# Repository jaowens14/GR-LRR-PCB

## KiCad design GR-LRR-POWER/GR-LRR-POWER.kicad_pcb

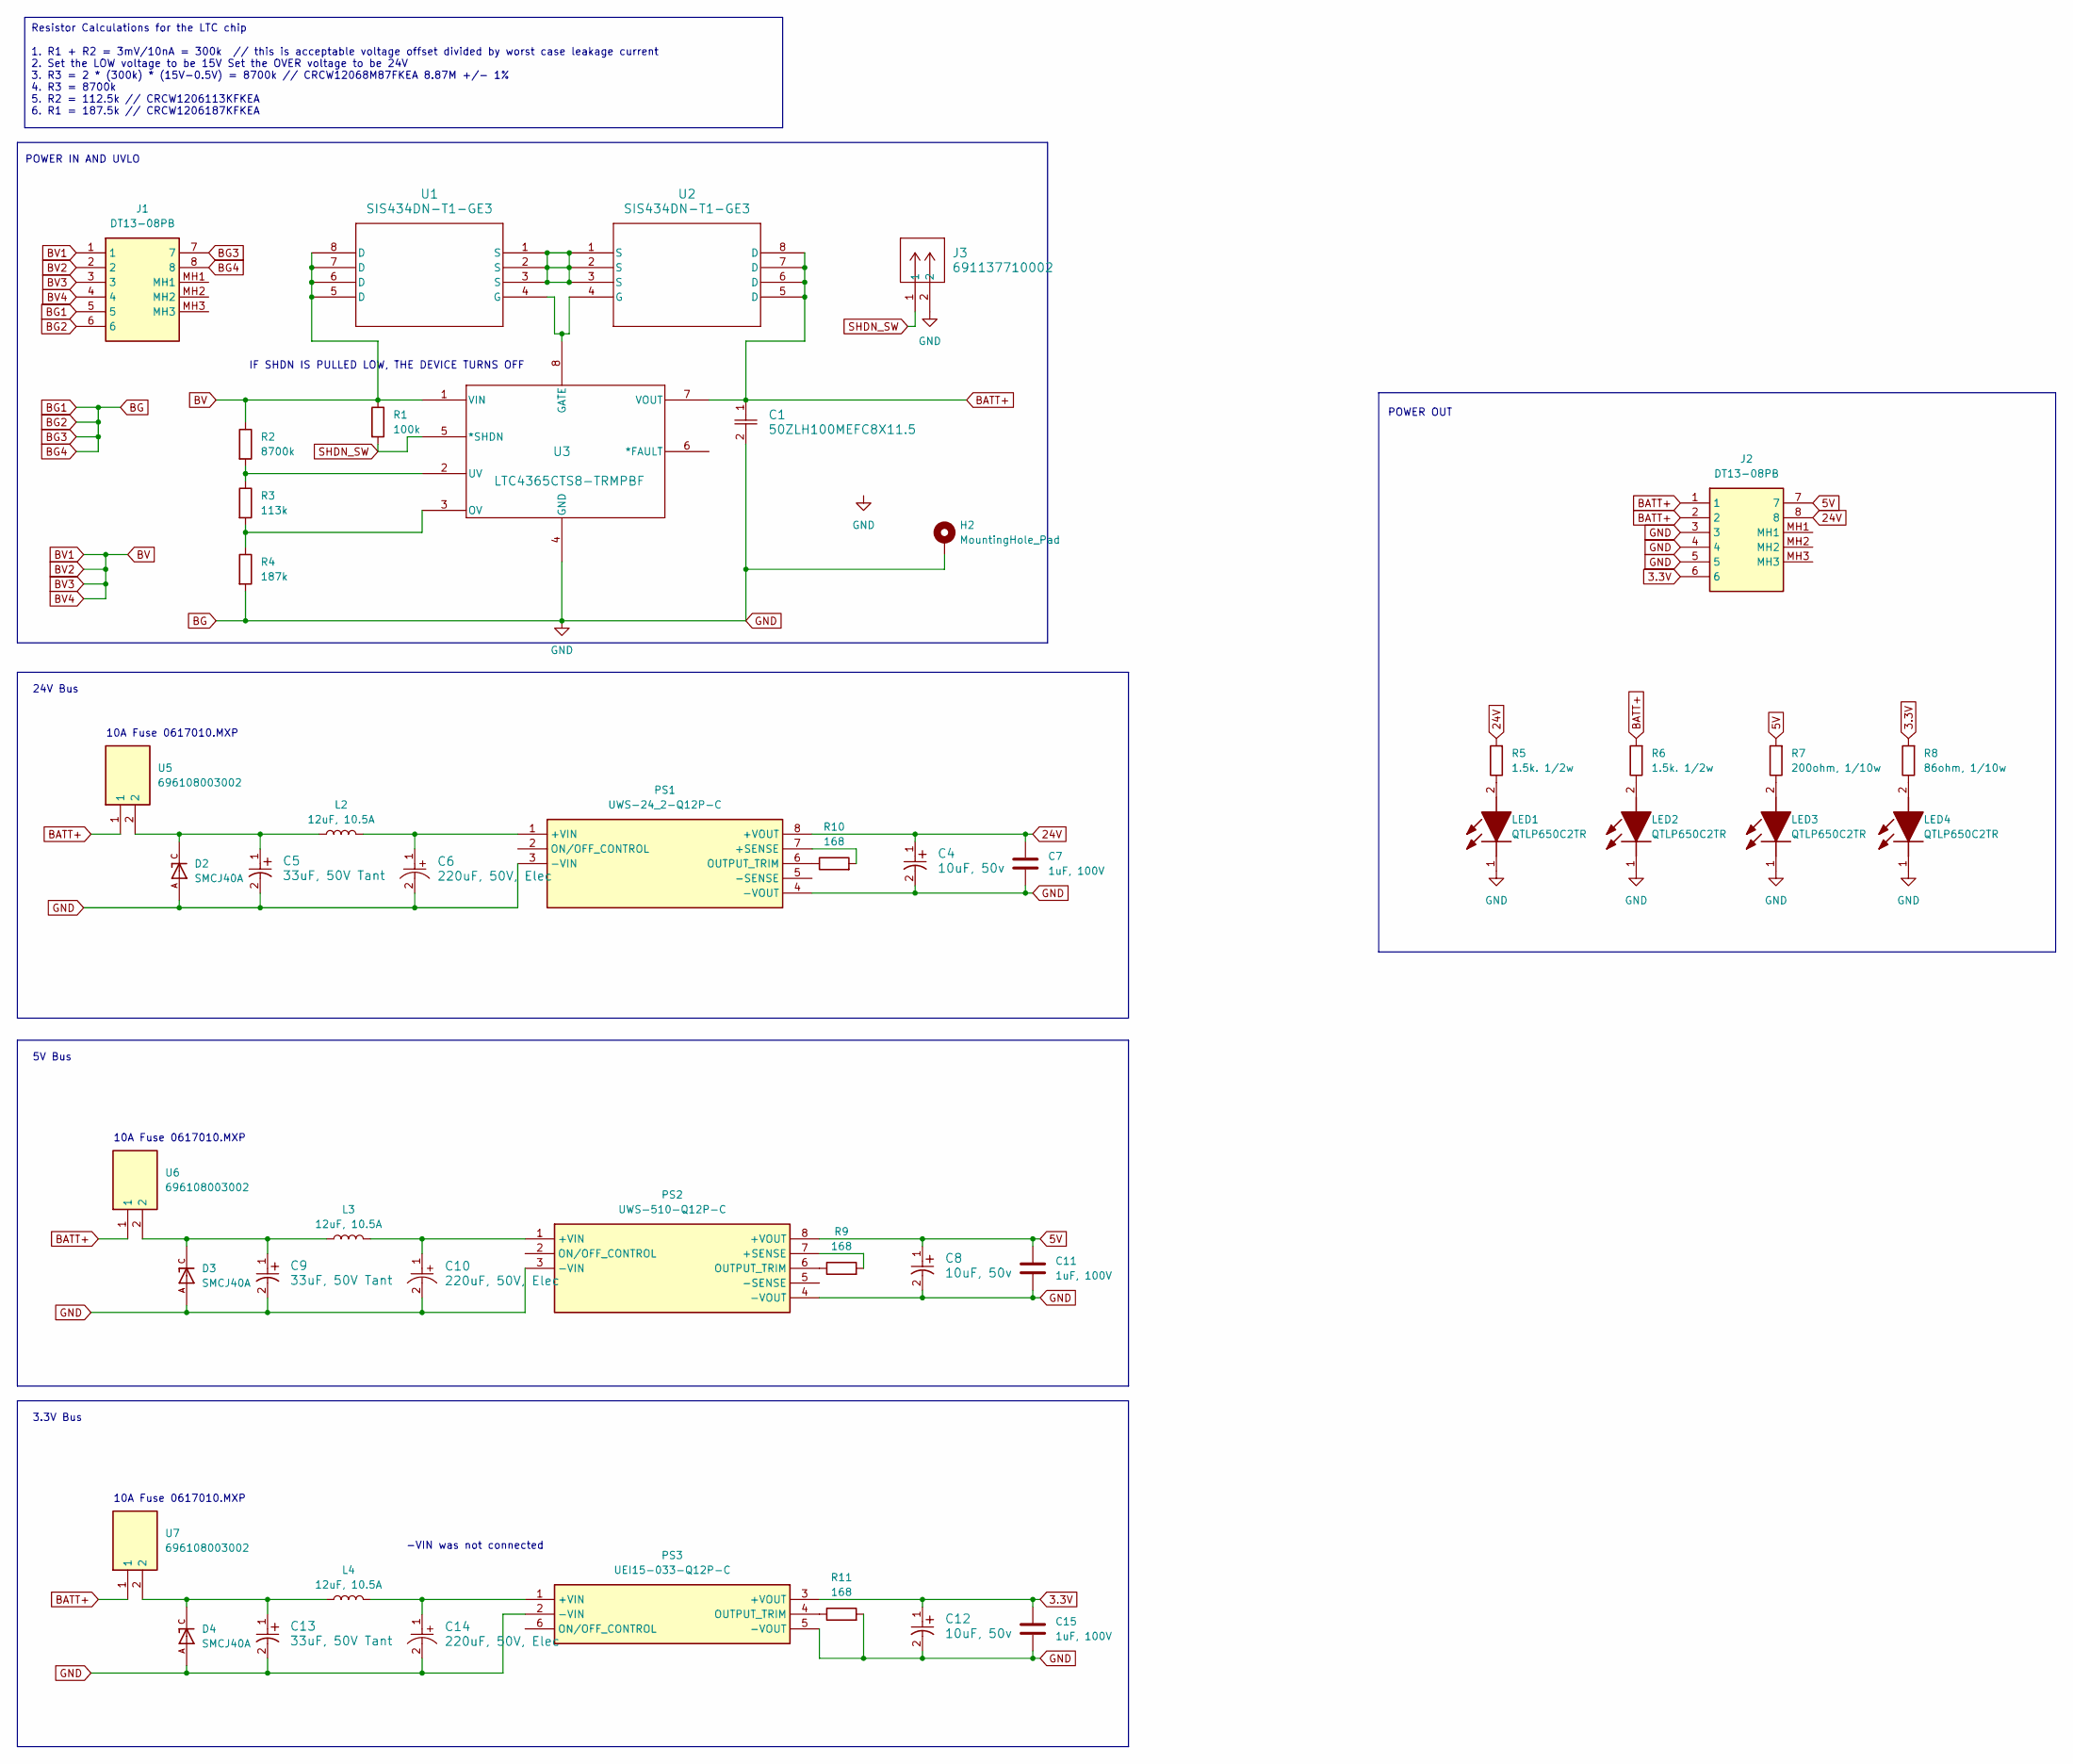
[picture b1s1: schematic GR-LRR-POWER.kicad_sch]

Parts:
C1: 50ZLH100MEFC8X11.5; 50ZLH100MEFC8X11_5; Part Number 50ZLH100MEFC8X11.5
C4, C8, C12: 10uF, 50v; PCAP_6.3x5.4-ELECT_NCA-L; Part Number UWZ1H100MCL1GB
C5, C9, C13: 33uF, 50V Tant; CAPMP7.6X4.3_4.3N_KEM-L; Part Number T521X336M050ATE050
C6, C10, C14: 220uF, 50V, Elec; U2-R_NCH-L; Part Number UWT1H221MNL1GS
C7, C11, C15: 1uF, 100V; C_1206_3216Metric_Pad1.33x1.80mm_HandSolder; Part Number CL31B105KCHNNNE
D2, D3, D4: SMCJ40A; DIOM7959X262N; PARTREV 11/20/15
H2: MountingHole_Pad; MountingHole_3mm_Pad_Via
J1, J2: DT13-08PB; DT1308PB; Mouser Part Number 571-DT13-08PB
J3: 691137710002; Part Number 691137710002
L2, L3, L4: 12uF, 10.5A; L_Coilcraft_XAL8080-XXX; Part Number XAL8080-123
LED1, LED2, LED3, LED4: QTLP650C2TR; LEDC3216X130N; Mouser Part Number 638-QTLP650C2
PS1: UWS-24_2-Q12P-C; UWS242Q12PC; Mouser Part Number 580-UWS-24/2-Q12P-C
PS2: UWS-510-Q12P-C; Mouser Part Number 580-UWS-15/3-Q12P-C
PS3: UEI15-033-Q12P-C; UEI15033Q12PC; Mouser Part Number 580-UEI15-033-Q12P-C
R1: 100k; R_1206_3216Metric_Pad1.30x1.75mm_HandSolder; Part Number CRCW12068M87FKEA
R2: 8700k; R_1206_3216Metric_Pad1.30x1.75mm_HandSolder; Part Number CRCW12068M87FKEA
R3: 113k; R_1206_3216Metric_Pad1.30x1.75mm_HandSolder; Part Number CRCW1206113KFKEA
R4: 187k; R_1206_3216Metric_Pad1.30x1.75mm_HandSolder; Part Number CRCW1206187KFKEA
R5, R6: 1.5k. 1/2w; R_1206_3216Metric_Pad1.30x1.75mm_HandSolder; Part Number RNCP1206FTD1K50
R7: 200ohm, 1/10w; R_1206_3216Metric_Pad1.30x1.75mm_HandSolder; Part Number RMCF1206JT200R
R8: 86ohm, 1/10w; R_1206_3216Metric_Pad1.30x1.75mm_HandSolder; Part Number RC1206FR-0786R6L
R9, R10, R11: 168; R_1206_3216Metric_Pad1.30x1.75mm_HandSolder
U1, U2: SIS434DN-T1-GE3; MOSFET_4DN-T1-E3_VIS; Part Number SIS434DN-T1-GE3
U3: LTC4365CTS8-TRMPBF; TSOT-23_TS8_LIT; Part Number LTC4365CTS8-TRMPBF
U5, U6, U7: 696108003002; WR-FSH_THT_2; Mouser Part Number 710-696108003002

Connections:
3.3V: C12.1, C15.1, J2.6, PS3.3 (+VOUT), R8.2
5V: C8.1, C11.1, J2.7, PS2.8 (+VOUT), R7.2
24V: C4.1, C7.1, J2.8, PS1.8 (+VOUT), R5.2
BATT+: C1.1, J2.1, J2.2, R6.2, U2.5 (D), U2.6 (D), U2.7 (D), U2.8 (D), U3.7 (VOUT), U5.1, U6.1, U7.1
BG: C1.2, C4.2, C5.2, C6.2, C7.2, C8.2, C9.2, C10.2, C11.2, C12.2, C13.2, C14.2, C15.2, D2.A, D3.A, D4.A, H2.1, J1.5, J1.6, J1.7, J1.8, J2.3, J2.4, J2.5, J3.2, LED1.1 (K), LED2.1 (K), LED3.1 (K), LED4.1 (K), PS1.3 (-VIN), PS1.4 (-VOUT), PS2.3 (-VIN), PS2.4 (-VOUT), PS3.2 (-VIN), PS3.5 (-VOUT), R4.2, R11.2, U3.4 (GND)
BV: J1.1, J1.2, J1.3, J1.4, R1.1, R2.1, U1.5 (D), U1.6 (D), U1.7 (D), U1.8 (D), U3.1 (VIN)
unnamed: C5.1, D2.C, L2.1, U5.2
unnamed: C9.1, D3.C, L3.1, U6.2
unnamed: C13.1, D4.C, L4.1, U7.2
unnamed: LED1.2 (A), R5.1
unnamed: LED2.2 (A), R6.1
unnamed: LED3.2 (A), R7.1
unnamed: LED4.2 (A), R8.1
unnamed: PS1.7 (+SENSE), R10.2
unnamed: C6.1, L2.2, PS1.1 (+VIN)
unnamed: PS1.6 (OUTPUT_TRIM), R10.1
unnamed: PS2.7 (+SENSE), R9.2
unnamed: C10.1, L3.2, PS2.1 (+VIN)
unnamed: PS2.6 (OUTPUT_TRIM), R9.1
unnamed: C14.1, L4.2, PS3.1 (+VIN)
unnamed: PS3.4 (OUTPUT_TRIM), R11.1
unnamed: U1.4 (G), U2.4 (G), U3.8 (GATE)
unnamed: U1.1 (S), U1.2 (S), U1.3 (S), U2.1 (S), U2.2 (S), U2.3 (S)
unnamed: R3.2, R4.1, U3.3 (OV)
unnamed: R2.2, R3.1, U3.2 (UV)
SHDN_SW: J3.1, R1.2, U3.5 (*SHDN)

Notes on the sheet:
Resistor Calculations for the LTC chip 1. R1 + R2 = 3mV/10nA = 300k // this is acceptable voltage offset divided by worst case leakage current 2. Set the LOW voltage to be 15V Set the OVER voltage to be 24V 3. R3 = 2 * (300k) * (15V-0.5V) = 8700k // CRCW12068M87FKEA 8.87M +/- 1% 4. R3 = 8700k 5. R2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
10A Fuse 0617010.MXP
3.3V Bus
POWER IN AND UVLO
POWER OUT
24V Bus
5V Bus
-VIN was not connected
IF SHDN IS PULLED LOW, THE DEVICE TURNS OFF

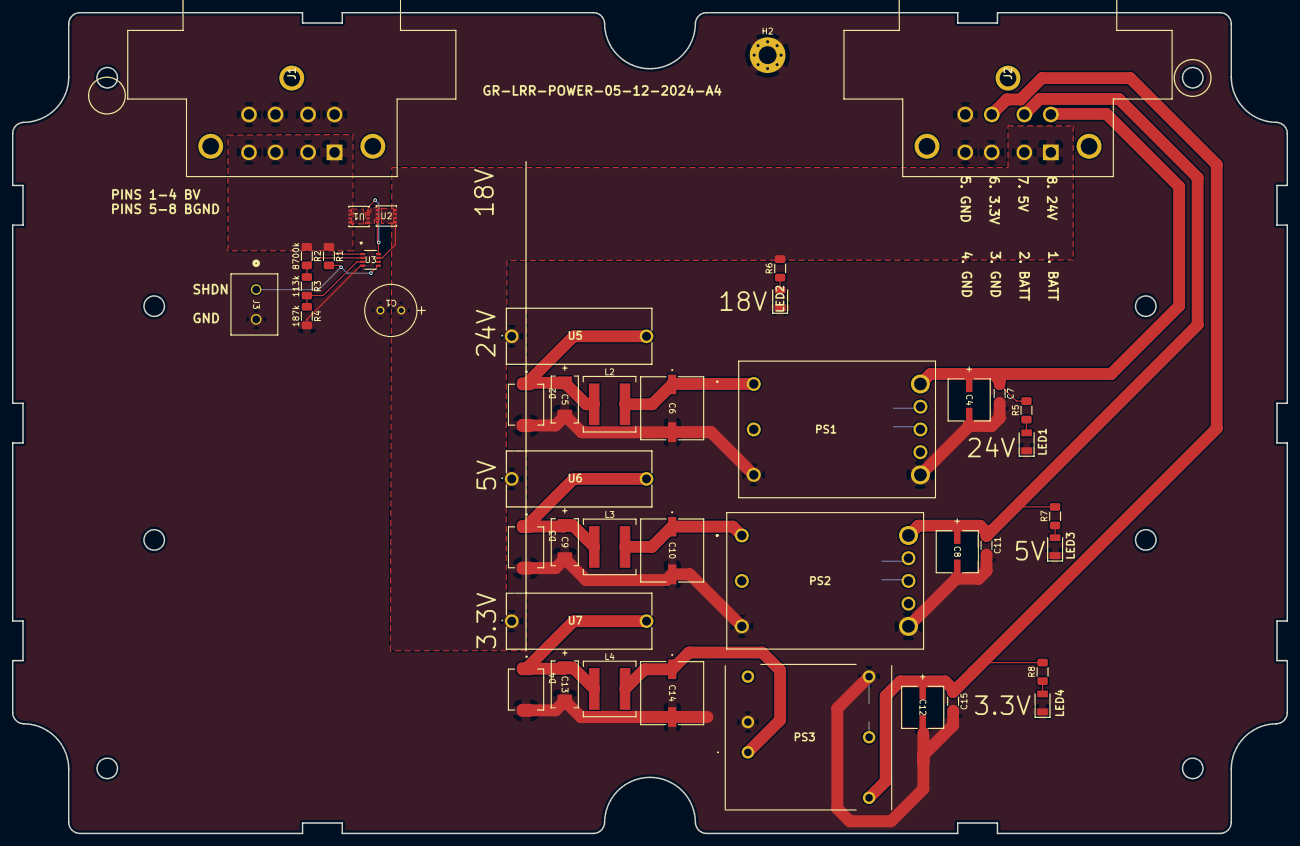
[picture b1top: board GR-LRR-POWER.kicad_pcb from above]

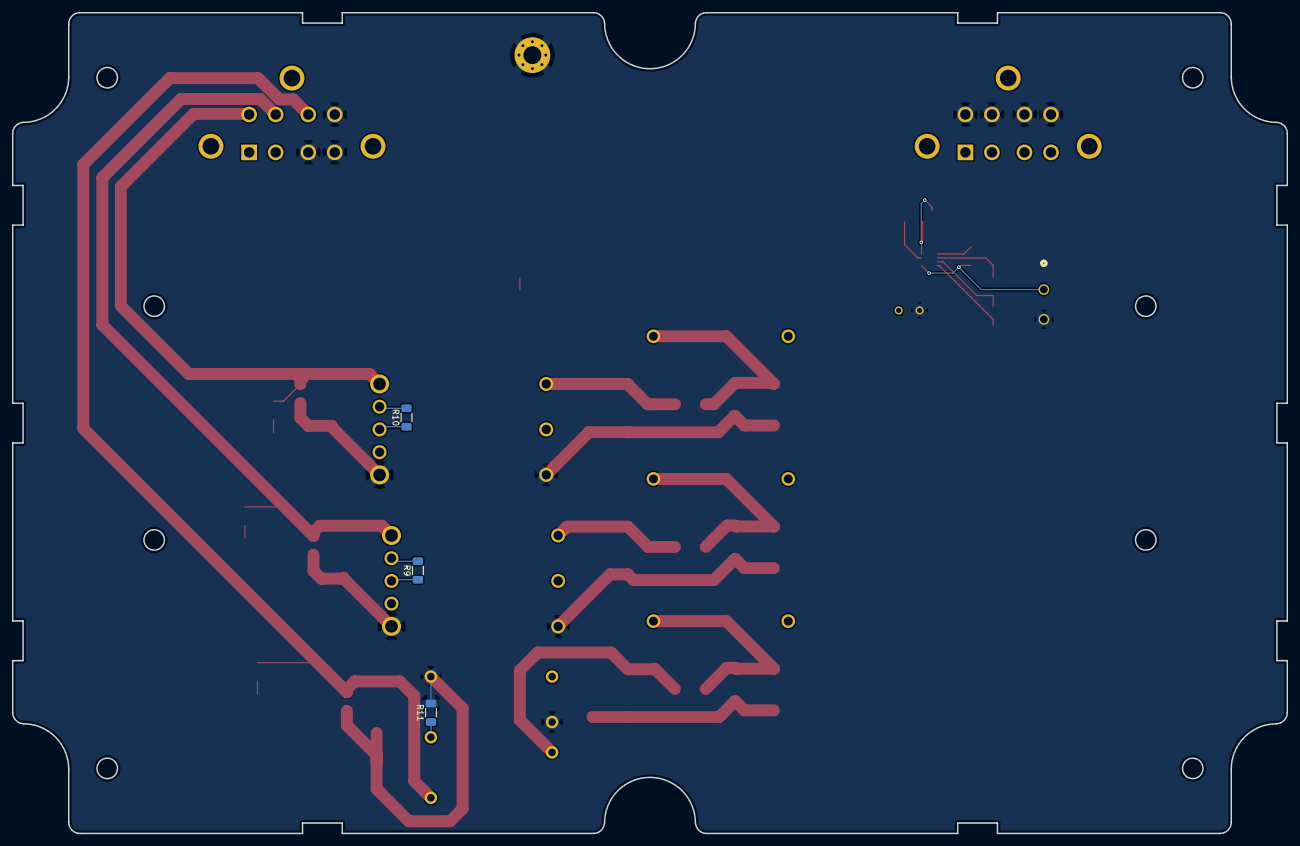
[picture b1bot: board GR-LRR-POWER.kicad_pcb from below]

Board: 2 copper layers, 213.7 x 137.6 mm, 47 parts (3 on the bottom side), 26 nets.

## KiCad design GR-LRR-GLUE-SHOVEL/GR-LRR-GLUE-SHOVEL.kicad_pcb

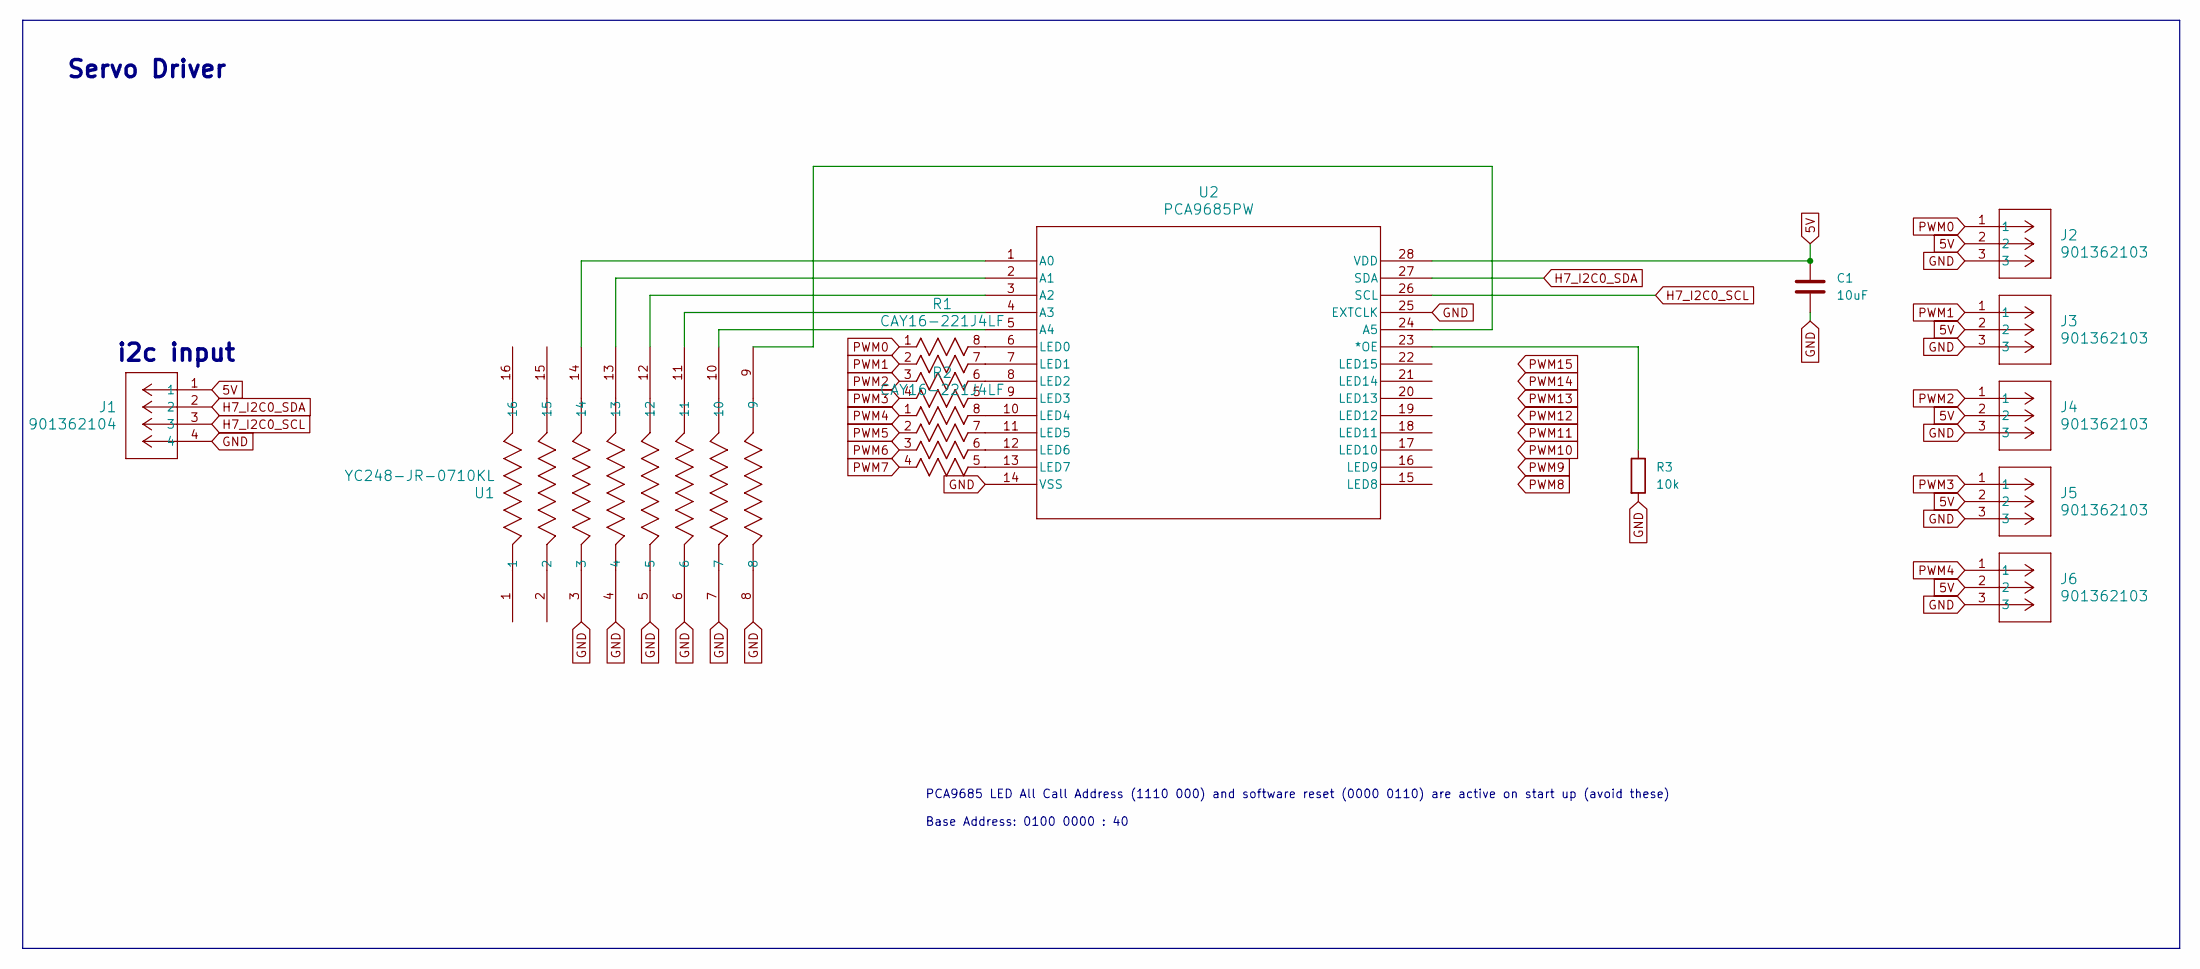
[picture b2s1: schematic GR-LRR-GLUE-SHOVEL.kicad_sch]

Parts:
C1: 10uF; C_1206_3216Metric_Pad1.33x1.80mm_HandSolder
J1: 901362104
J2, J3, J4, J5, J6: 901362103
R1, R2: CAY16-221J4LF; CAY16_221J4LF
R3: 10k; R_1206_3216Metric_Pad1.30x1.75mm_HandSolder
U1: YC248-JR-0710KL; RES_YC248_4X1P6_YAG
U2: PCA9685PW; SOT361-1_NXP

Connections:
5V: C1.1, J1.1, J2.2, J3.2, J4.2, J5.2, J6.2, U2.28 (VDD)
GND: C1.2, J1.4, J2.3, J3.3, J4.3, J5.3, J6.3, R3.2, U1.3, U1.4, U1.5, U1.6, U1.7, U1.8, U2.14 (VSS), U2.25 (EXTCLK)
H7_I2C0_SCL: J1.3, U2.26 (SCL)
H7_I2C0_SDA: J1.2, U2.27 (SDA)
unnamed: R3.1, U2.23 (*OE)
unnamed: U1.14, U2.1 (A0)
unnamed: U1.13, U2.2 (A1)
unnamed: U1.12, U2.3 (A2)
unnamed: U1.11, U2.4 (A3)
unnamed: U1.10, U2.5 (A4)
unnamed: U1.9, U2.24 (A5)
unnamed: R1.8, U2.6 (LED0)
unnamed: R1.7, U2.7 (LED1)
unnamed: R1.6, U2.8 (LED2)
unnamed: R1.5, U2.9 (LED3)
unnamed: R2.8, U2.10 (LED4)
unnamed: R2.7, U2.11 (LED5)
unnamed: R2.6, U2.12 (LED6)
unnamed: R2.5, U2.13 (LED7)
PWM0: J2.1, R1.1
PWM1: J3.1, R1.2
PWM2: J4.1, R1.3
PWM3: J5.1, R1.4
PWM4: J6.1, R2.1
PWM5: R2.2
PWM6: R2.3
PWM7: R2.4

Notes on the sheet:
PCA9685 LED All Call Address (1110 000) and software reset (0000 0110) are active on start up (avoid these) Base Address: 0100 0000 : 40
Servo Driver
i2c input

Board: 2 copper layers, 12 parts (0 on the bottom side), 24 nets, no tracks yet.

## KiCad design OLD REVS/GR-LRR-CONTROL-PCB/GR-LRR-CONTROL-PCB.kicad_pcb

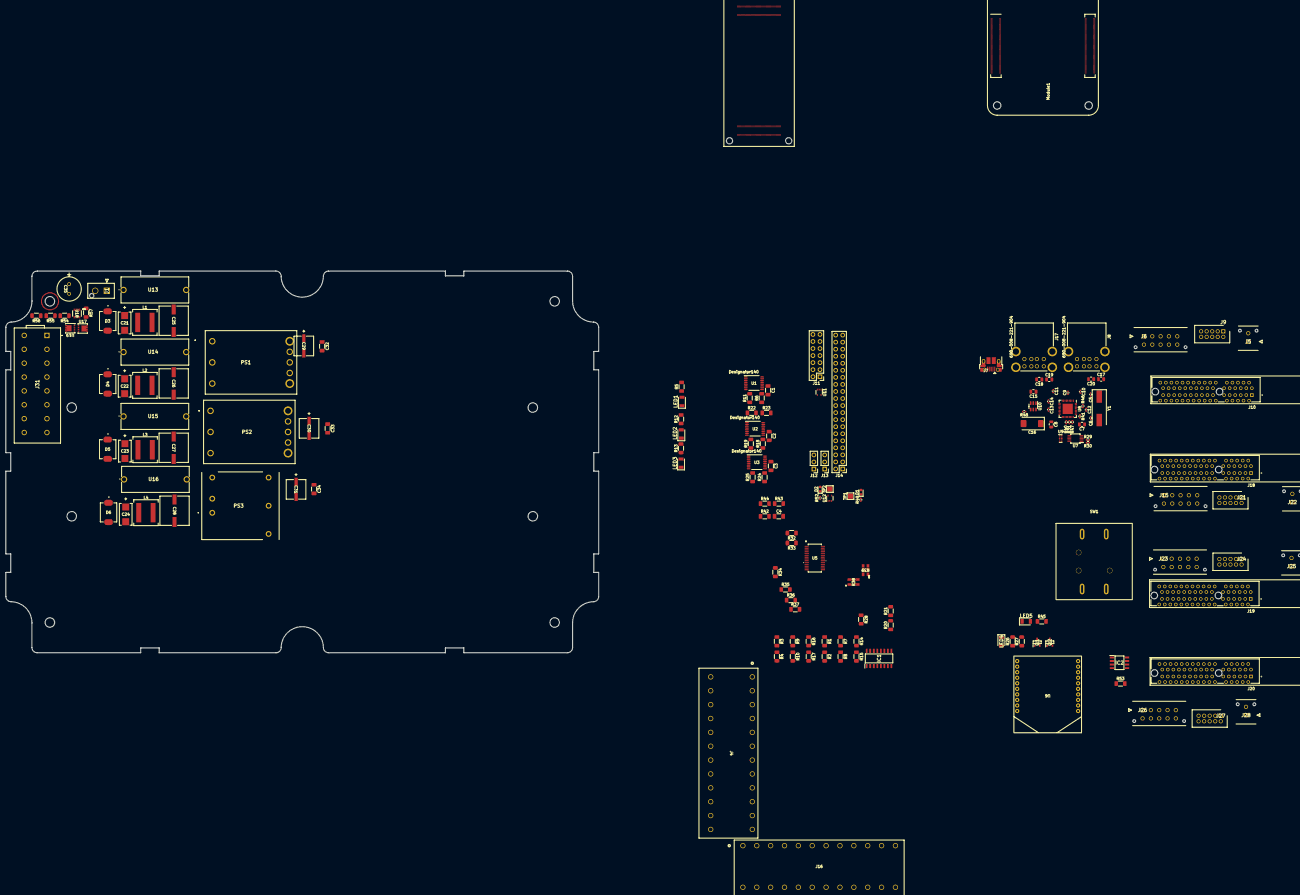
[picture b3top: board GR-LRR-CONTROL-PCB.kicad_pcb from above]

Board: 2 copper layers, 213.7 x 137.6 mm, 163 parts (0 on the bottom side), 228 nets, no tracks yet.

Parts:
C1, C2, C3: 0.1uF; C_1206_3216Metric_Pad1.33x1.80mm_HandSolder
C4: 10uF; C_1206_3216Metric_Pad1.33x1.80mm_HandSolder
C5, C6: 27pF; C_0402_1005Metric
C7, C8, C15, C17, C18, C19, C20: 10u; C_0805_2012Metric
C9, C10, C11, C12, C13, C14: 100n; C_0402_1005Metric
C16: 100uF; CP_EIA-7343-31_Kemet-D
C21, C22, C23, C24: 33uF, 50V Tant; CAPMP7.6X4.3_4.3N_KEM
C25, C26, C27, C28: 220uF, 50V, Elec; U2-R_NCH
C29, C30, C31: 10uF, 50v; PCAP_6.3x5.4-ELECT_NCA
C32, C33, C34: 1uF, 100V; C_1206_3216Metric_Pad1.33x1.80mm_HandSolder
C35: 50ZLH100MEFC8X11.5; CAP_YX_8X11P5_RUB
D1: LED Green; LED_0603_1608Metric
D2: LED Red; LED_0603_1608Metric
D3, D4, D5, D6: SMCJ40A; DIOM7959X262N
IC1: MC1413DR2G; SOIC127P600X175-16N
IC2: TJA1049T,118
J1: Switch; 212520-1002
J4, J16: 736-112; CONN24_736-112_WAG
J5, J22, J25, J28: 43045-0212; 43045-02YY_121314
J6, J15, J23, J26: 43045-1012; 43045-10YY_121314
J7: USB_OTG; USB_Micro-B_EDAC_UCON00686
J8, J17: 690-008-221-904; MOLEX_USB_67298-4090
J9, J21, J24, J27: 87831-1019
J10, J18, J19, J20: 10018783-10101TLF; AMPHENOL_10018783-10101TLF
J11: Conn_02x07_Odd_Even; PinHeader_2x07_P2.54mm_Vertical
J12, J13: Conn_01x03; PinHeader_1x03_P2.54mm_Vertical
J14: THD-20-R; PinHeader_2x20_P2.54mm_Vertical
J31: 2604-3108; 26043108
L1, L2, L3, L4: 12uF, 10.5A; L_Coilcraft_XAL8080-XXX
LED1, LED2, LED3, LED4, LED5: QTLP650C2TR; LEDC3216X130N
Module1: ComputeModule4; Raspberry-Pi-4-Compute-Module
PS1: UWS-24_2-Q12P-C; UWS242Q12PC
PS2: UWS-510-Q12P-C
PS3: UEI15-033-Q12P-C; UEI15033Q12PC
Q1, Q2: BSS806NH6327XTSA1; SOT95P240X110-3N
R1, R3, R7, R9, R14, R16: 1k 1/8W; R_1206_3216Metric_Pad1.30x1.75mm_HandSolder
R2, R4, R8, R10, R15, R17: 2k 1/8w; R_1206_3216Metric_Pad1.30x1.75mm_HandSolder
R5: 1.5k. 1/2w; R_1206_3216Metric_Pad1.30x1.75mm_HandSolder
R6, R11, R18, R19, R24, R25, R32, R33, R34, R35, R36, R37, R42, R43, R44: 10k; R_1206_3216Metric_Pad1.30x1.75mm_HandSolder
R12: 200ohm, 1/10w; R_1206_3216Metric_Pad1.30x1.75mm_HandSolder
R13, R26, R45: 86ohm, 1/10w; R_1206_3216Metric_Pad1.30x1.75mm_HandSolder
R20: 4k; R_1206_3216Metric_Pad1.30x1.75mm_HandSolder
R21: 1k 1/8w; R_1206_3216Metric_Pad1.30x1.75mm_HandSolder
R22: 100k 1/8W; R_1206_3216Metric_Pad1.30x1.75mm_HandSolder
R23: 10k 1/8w; R_1206_3216Metric_Pad1.30x1.75mm_HandSolder
R27, R28: 10k 1/8W; R_1206_3216Metric_Pad1.30x1.75mm_HandSolder
R29, R30: 2.2K 1%; R_0402_1005Metric
R31, R40, R41, R47: 36K 1%; R_0402_1005Metric
R38, R39: CAY16-221J4LF; BO_CAY16
R46: 12K 1%; R_0402_1005Metric
R48: 15K 1%; R_0402_1005Metric
R49, R52: 1k; R_0402_1005Metric
R53: 120; R_1206_3216Metric_Pad1.30x1.75mm_HandSolder
R54: 8700k; R_1206_3216Metric_Pad1.30x1.75mm_HandSolder
R55: 113k; R_1206_3216Metric_Pad1.30x1.75mm_HandSolder
R56: 187k; R_1206_3216Metric_Pad1.30x1.75mm_HandSolder
R57: 100k; R_1206_3216Metric_Pad1.30x1.75mm_HandSolder
SW1: XA1E-BV302-R
TP1, TP2: TestPoint; TestPoint_Pad_2.0x2.0mm
U1, U2, U3: INA260AIPWR; PW0016A_N
U4: ABX00042; MODULE_ABX00042
U5: PCA9685PW; SOT361-1_NXP
U6: XB3-24AST-J
U7: FSUSB42MUX; MSOP-10_3x3mm_P0.5mm
U8: USB2514B-I/M2; QFN-36-1EP_6x6mm_P0.5mm_EP3.7x3.7mm
U9: TPD4EUSB30; USON-10_2.5x1.0mm_P0.5mm
U10: AP22653W6; SOT-23-6
U11, U12: 74LVC1G07SE-7; SOT-353_SC-70-5
U13, U14, U15, U16: 696108003002; WR-FSH_THT_2
U17, U19: SIS434DN-T1-GE3; MOSFET_4DN-T1-E3_VIS
U18: LTC4365CTS8-TRMPBF; TSOT-23_TS8_LIT
Y1: 24MHz; Crystal_SMD_HC49-SD

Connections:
3.3V: C31.1, C34.1, PS3.3 (+VOUT)
5V: C30.1, C33.1, PS2.8 (+VOUT)
18V: C25.1, L1.2
24V: C29.1, C32.1, PS1.8 (+VOUT)
73_ANALOG_A0: R22.2, R23.1, U4.J2_73 (ADC_A0)
75_ANALOG_A1: R20.2, R21.1, U4.J2_75 (ADC_A1)
+3.3V: IC2.5 (SPLIT), Q2.3 (D), R6.1, R11.1, R18.1, R19.1, R24.1, R25.1, R28.1, U3.14 (IN-), U3.15 (IN-), U3.16 (IN-), U6.1 (VCC)
+3.3V_IN: C1.2, C2.2, C3.2, R13.2, U1.10 (VS), U2.10 (VS), U3.1 (IN+), U3.2 (IN+), U3.3 (IN+), U3.5 (A0), U3.10 (VS), U3.12 (VBUS)
+5V: C4.1, IC2.3 (VCC), J4.1, J4.4, J4.7, J4.10, J4.13, J4.16, J4.19, J4.22, J16.15, J16.20, R42.1, R44.1, U2.14 (IN-), U2.15 (IN-), U2.16 (IN-), U4.J1_21 (VIN), U4.J1_41 (VIN), U5.28 (VDD)
+5V_IN: R12.2, U2.1 (IN+), U2.2 (IN+), U2.3 (IN+), U2.12 (VBUS)
+24V: J16.2, J16.4, J16.7, U1.14 (IN-), U1.15 (IN-), U1.16 (IN-)
+24V_IN: R5.2, U1.1 (IN+), U1.2 (IN+), U1.3 (IN+), U1.12 (VBUS)
/+3.3v: C7.1, C8.1, C9.1, C10.1, C11.1, C12.1, C13.1, C14.1, D1.2 (A), D2.2 (A), J14.1, J14.17, Module1.84 (+3.3v_(Output)), Module1.86 (+3.3v_(Output)), U7.1 (VCC), U8.5 (VDDA33), U8.10 (VDDA33), U8.15 (VDD33), U8.23 (VDD33), U8.27 (VBUS_DET), U8.29 (VDDA33), U8.36 (VDDA33), U12.5 (VCC)
/+5v: C15.1, J14.2, J14.4, Module1.77 (+5v_(Input)), Module1.79 (+5v_(Input)), Module1.81 (+5v_(Input)), Module1.83 (+5v_(Input)), Module1.85 (+5v_(Input)), Module1.87 (+5v_(Input)), U10.1 (IN), U11.5 (VCC)
/CM4_GPIO ( Ethernet, GPIO, SDCARD)/+1.8v: Module1.88 (+1.8v_(Output)), Module1.90 (+1.8v_(Output))
/CM4_GPIO ( Ethernet, GPIO, SDCARD)/AIN0: J11.5, Module1.96 (AnalogIP0)
/CM4_GPIO ( Ethernet, GPIO, SDCARD)/AIN1: J11.6, Module1.94 (AnalogIP1)
/CM4_GPIO ( Ethernet, GPIO, SDCARD)/BT_nDis: J12.3, Module1.91 (BT_nDisable)
/CM4_GPIO ( Ethernet, GPIO, SDCARD)/EEPROM_nWP: J11.4, Module1.20 (EEPROM_nWP)
/CM4_GPIO ( Ethernet, GPIO, SDCARD)/GLOBAL_EN: J11.14, J13.1, Module1.99 (Global_EN)
/CM4_GPIO ( Ethernet, GPIO, SDCARD)/GPIO2: J14.3, Module1.58 (GPIO2)
/CM4_GPIO ( Ethernet, GPIO, SDCARD)/GPIO3: J14.5, Module1.56 (GPIO3)
/CM4_GPIO ( Ethernet, GPIO, SDCARD)/GPIO4: J14.7, Module1.54 (GPIO4)
/CM4_GPIO ( Ethernet, GPIO, SDCARD)/GPIO5: J14.29, Module1.34 (GPIO5)
/CM4_GPIO ( Ethernet, GPIO, SDCARD)/GPIO6: J14.31, Module1.30 (GPIO6)
/CM4_GPIO ( Ethernet, GPIO, SDCARD)/GPIO7: J14.26, Module1.37 (GPIO7)
/CM4_GPIO ( Ethernet, GPIO, SDCARD)/GPIO8: J14.24, Module1.39 (GPIO8)
/CM4_GPIO ( Ethernet, GPIO, SDCARD)/GPIO9: J14.21, Module1.40 (GPIO9)
/CM4_GPIO ( Ethernet, GPIO, SDCARD)/GPIO10: J14.19, Module1.44 (GPIO10)
/CM4_GPIO ( Ethernet, GPIO, SDCARD)/GPIO11: J14.23, Module1.38 (GPIO11)
/CM4_GPIO ( Ethernet, GPIO, SDCARD)/GPIO12: J14.32, Module1.31 (GPIO12)
/CM4_GPIO ( Ethernet, GPIO, SDCARD)/GPIO13: J14.33, Module1.28 (GPIO13)
/CM4_GPIO ( Ethernet, GPIO, SDCARD)/GPIO16: J14.36, Module1.29 (GPIO16)
/CM4_GPIO ( Ethernet, GPIO, SDCARD)/GPIO17: J14.11, Module1.50 (GPIO17)
/CM4_GPIO ( Ethernet, GPIO, SDCARD)/GPIO18: J14.12, Module1.49 (GPIO18)
/CM4_GPIO ( Ethernet, GPIO, SDCARD)/GPIO19: J14.35, Module1.26 (GPIO19)
/CM4_GPIO ( Ethernet, GPIO, SDCARD)/GPIO20: J14.38, Module1.27 (GPIO20)
/CM4_GPIO ( Ethernet, GPIO, SDCARD)/GPIO21: J14.40, Module1.25 (GPIO21)
/CM4_GPIO ( Ethernet, GPIO, SDCARD)/GPIO22: J14.15, Module1.46 (GPIO22)
/CM4_GPIO ( Ethernet, GPIO, SDCARD)/GPIO23: J14.16, Module1.47 (GPIO23)
/CM4_GPIO ( Ethernet, GPIO, SDCARD)/GPIO24: J14.18, Module1.45 (GPIO24)
/CM4_GPIO ( Ethernet, GPIO, SDCARD)/GPIO25: J14.22, Module1.41 (GPIO25)
/CM4_GPIO ( Ethernet, GPIO, SDCARD)/GPIO26: J14.37, Module1.24 (GPIO26)
/CM4_GPIO ( Ethernet, GPIO, SDCARD)/GPIO27: J14.13, Module1.48 (GPIO27)
/CM4_GPIO ( Ethernet, GPIO, SDCARD)/ID_SC: J14.28, Module1.35 (ID_SC)
/CM4_GPIO ( Ethernet, GPIO, SDCARD)/ID_SD: J14.27, Module1.36 (ID_SD)
/CM4_GPIO ( Ethernet, GPIO, SDCARD)/RUN_PG: J13.3, Module1.92 (RUN_PG), U11.2
/CM4_GPIO ( Ethernet, GPIO, SDCARD)/SYNC_IN: J11.8, Module1.16 (Ethernet_SYNC_IN(1.8v))
/CM4_GPIO ( Ethernet, GPIO, SDCARD)/SYNC_OUT: J11.9, Module1.18 (Ethernet_SYNC_OUT(1.8v))
/CM4_GPIO ( Ethernet, GPIO, SDCARD)/TV_OUT: J11.11, Module1.111 (VDAC_COMP)
/CM4_GPIO ( Ethernet, GPIO, SDCARD)/WL_nDis: J12.1, Module1.89 (WL_nDisable)
/CM4_GPIO ( Ethernet, GPIO, SDCARD)/nPWR_LED: Module1.95 (nPI_LED_PWR), U12.2
/CM4_GPIO ( Ethernet, GPIO, SDCARD)/nRPIBOOT: J11.2, Module1.93 (nRPIBOOT)
/CM4_HighSpeed/USB2_N: Module1.103 (USB2_N), U7.4 (D_N)
/CM4_HighSpeed/USB2_P: Module1.105 (USB2_P), U7.3 (D_P)
/CM4_HighSpeed/USBOTG_ID: Module1.101 (USB_OTG_ID), R29.1, R30.2, U7.2 (SEL)
/USB2-HUB/HD1_N: J8.2 (D-`), U8.1 (USBDM_DN1/PRT_DIS_M1)
/USB2-HUB/HD1_P: J8.3 (D+`), U8.2 (USBDP_DN1/PRT_DIS_P1)
/USB2-HUB/HD2_N: J8.6 (D-), U8.3 (USBDM_DN2/PRT_DIS_M2)
/USB2-HUB/HD2_P: J8.7 (D+), U8.4 (USBDP_DN2/PRT_DIS_P2)
/USB2-HUB/HD3_N: J17.2 (D-`), U8.6 (USBDM_DN3/PRT_DIS_M3)
/USB2-HUB/HD3_P: J17.3 (D+`), U8.7 (USBDP_DN3/PRT_DIS_P3)
/USB2-HUB/HD4_N: J17.6 (D-), U8.8 (USBDM_DN4/PRT_DIS_M4)
/USB2-HUB/HD4_P: J17.7 (D+), U8.9 (USBDP_DN4/PRT_DIS_P4)
/USB2-HUB/PWR1: U8.12 (PRTPWR1/BC_EN1), U10.3 (EN)
/USB2-HUB/USBD_N: J7.2 (D-), U7.8 (HSD1_M), U9.4 (D2+), U9.7
/USB2-HUB/USBD_P: J7.3 (D+), U7.9 (HSD1_P), U9.5 (D2-), U9.6
/USB2-HUB/USBH_N: U7.6 (HSD0_M), U8.30 (USBDM_UP)
/USB2-HUB/USBH_P: U7.7 (HSD0_P), U8.31 (USBDP_UP)
/USB2-HUB/VBUS: C16.1, C17.1, C18.1, C19.1, C20.1, J8.1 (VBUS`), J8.5 (VBUS), J17.1 (VBUS`), J17.5 (VBUS), U10.6 (OUT)
/USB2-HUB/nOCS1: U8.13 (OCS_N1), U8.17 (OCS_N2), U8.19 (OCS_N3), U8.21 (OCS_N4), U10.4 (nFault)
/nEXTRST: Module1.100 (nEXTRST), U8.26 (RESET_N)
BATT+: J1.1, R22.1, U13.1, U14.1, U15.1, U16.1
BG: C35.2, J31.3 (2.1), J31.4 (2.2), J31.7 (4.1), J31.8 (4.2), J31.11 (6.1), J31.12 (6.2), J31.15 (8.1), J31.16 (8.2), R56.2, U18.4 (GND)
BV: J31.1 (1.1), J31.2 (1.2), J31.5 (3.1), J31.6 (3.2), J31.9 (5.1), J31.10 (5.2), J31.13 (7.1), J31.14 (7.2), R54.1, R57.2, U17.5 (D), U17.6 (D), U17.7 (D), U17.8 (D), U18.1 (VIN)
CLAMP_C: J16.6, R28.2, U4.J2_61 (PWM_2)
D0 STEPPER ENABLE: Q1.1 (G), U4.J2_62 (PWM_7)
DVR_+5VOUT_1: J6.8, J9.2, J9.4, J10.A11, J10.B11
DVR_+5VOUT_2: J15.8, J18.A11, J18.B11, J21.2, J21.4
DVR_+5VOUT_3: J19.A11, J19.B11, J23.8, J24.2, J24.4
DVR_+5VOUT_4: J20.A11, J20.B11, J26.8, J27.2, J27.4
DVR_+Vmot_1: J5.2, J10.A21, J10.A22, J10.B21, J10.B22
DVR_+Vmot_2: J18.A21, J18.A22, J18.B21, J18.B22, J22.2
DVR_+Vmot_3: J19.A21, J19.A22, J19.B21, J19.B22, J25.2
DVR_+Vmot_4: J20.A21, J20.A22, J20.B21, J20.B22, J28.2
DVR_A-/SIN-/LH1_1: J9.5, J10.A13
DVR_A-/SIN-/LH1_2: J18.B13, J21.5
DVR_A-/SIN-/LH1_3: J19.B13, J24.5
DVR_A-/SIN-/LH1_4: J20.B13, J27.5
DVR_A/A+_1: J6.1, J10.B29, J10.B30, J10.B31, J10.B32
DVR_A/A+_2: J15.1, J18.A29, J18.A30, J18.A31, J18.A32
DVR_A/A+_3: J19.A29, J19.A30, J19.A31, J19.A32, J23.1
DVR_A/A+_4: J20.A29, J20.A30, J20.A31, J20.A32, J26.1
DVR_A/SIN+_1: J9.6, J10.A14
DVR_A/SIN+_2: J18.B14, J21.6
DVR_A/SIN+_3: J19.B14, J24.6
DVR_A/SIN+_4: J20.B14, J27.6
DVR_B-/COS-/LH2_1: J9.7, J10.A15
DVR_B-/COS-/LH2_2: J18.B15, J21.7
DVR_B-/COS-/LH2_3: J19.B15, J24.7
DVR_B-/COS-/LH2_4: J20.B15, J27.7
DVR_BR/B-_1: J6.7, J10.A25, J10.A26, J10.A27, J10.A28
DVR_BR/B-_2: J15.7, J18.B25, J18.B26, J18.B27, J18.B28
DVR_BR/B-_3: J19.B25, J19.B26, J19.B27, J19.B28, J23.7
DVR_BR/B-_4: J20.B25, J20.B26, J20.B27, J20.B28, J26.7
DVR_B/A-_1: J6.6, J10.A29, J10.A30, J10.A31, J10.A32
DVR_B/A-_2: J15.6, J18.B29, J18.B30, J18.B31, J18.B32
DVR_B/A-_3: J19.B29, J19.B30, J19.B31, J19.B32, J23.6
DVR_B/A-_4: J20.B29, J20.B30, J20.B31, J20.B32, J26.6
DVR_B/COS+_1: J9.8, J10.A16
DVR_B/COS+_2: J18.B16, J21.8
DVR_B/COS+_3: J19.B16, J24.8
DVR_B/COS+_4: J20.B16, J27.8
DVR_CAN_Hi_1: IC2.7 (CANH), J10.A19, J18.B19, J19.B19, J20.B19, R53.1
DVR_CAN_Lo_1: IC2.6 (CANL), J10.B19, J18.A19, J19.A19, J20.A19, R53.2
DVR_C/B+_1: J6.2, J10.B25, J10.B26, J10.B27, J10.B28
DVR_C/B+_2: J15.2, J18.A25, J18.A26, J18.A27, J18.A28
DVR_C/B+_3: J19.A25, J19.A26, J19.A27, J19.A28, J23.2
DVR_C/B+_4: J20.A25, J20.A26, J20.A27, J20.A28, J26.2
DVR_HALL1_1: J6.3, J10.A8
DVR_HALL1_2: J15.3, J18.B8
DVR_HALL1_3: J19.B8, J23.3
DVR_HALL1_4: J20.B8, J26.3
DVR_HALL2_1: J6.4, J10.A9
DVR_HALL2_2: J15.4, J18.B9
DVR_HALL2_3: J19.B9, J23.4
DVR_HALL2_4: J20.B9, J26.4
DVR_HALL3_1: J6.5, J10.A10
DVR_HALL3_2: J15.5, J18.B10
DVR_HALL3_3: J19.B10, J23.5
DVR_HALL3_4: J20.B10, J26.5
DVR_Z+_1: J9.10, J10.A18
DVR_Z+_2: J18.B18, J21.10
DVR_Z+_3: J19.B18, J24.10
DVR_Z+_4: J20.B18, J27.10
DVR_Z-/LH3_1: J9.9, J10.A17
DVR_Z-/LH3_2: J18.B17, J21.9
DVR_Z-/LH3_3: J19.B17, J24.9
DVR_Z-/LH3_4: J20.B17, J27.9
ENCODER1_PHASEA: R14.2, R15.1, U4.J2_16 (CAM_D0)
ENCODER1_PHASEA_IN: J16.19, R14.1
ENCODER1_PHASEB: R7.2, R8.1, U4.J2_14 (CAM_D1)
ENCODER1_PHASEB_IN: J16.18, R7.1
ENCODER1_PHASEZ: R1.2, R2.1, U4.J2_12 (CAM_D2)
ENCODER1_PHASEZ_IN: J16.17, R1.1
ENCODER2_PHASEA: R16.2, R17.1, U4.J2_10 (CAM_D3)
ENCODER2_PHASEA_IN: J16.14, R16.1
ENCODER2_PHASEB: R9.2, R10.1, U4.J2_8 (CAM_D4)
ENCODER2_PHASEB_IN: J16.13, R9.1
ENCODER2_PHASEZ: R3.2, R4.1, U4.J2_6 (CAM_D5)
ENCODER2_PHASEZ_IN: J16.12, R3.1
GND: C1.1, C2.1, C3.1, C4.2, C5.2, C6.2, C7.2, C8.2, C9.2, C10.2, C11.2, C12.2, C13.2, C14.2, C15.2, C16.2, C17.2, C18.2, C19.2, C20.2, C21.2, C22.2, C23.2, C24.2, C25.2, C26.2, C27.2, C28.2, C29.2, C30.2, C31.2, C32.2, C33.2, C34.2, D3.A, D4.A, D5.A, D6.A, IC1.8 (GND), IC2.2 (GND), J4.3, J4.6, J4.9, J4.12, J4.15, J4.18, J4.21, J4.24, J5.1, J6.9, J6.10, J7.5 (GND), J7.6 (Shield), J8.4 (GND`), J8.8 (GND), J8.MT1, J8.MT2, J8.MT3, J8.MT4, J9.1, J9.3, J10.A1, J10.A12, J10.A20, J10.A23, J10.A24, J10.B1, J10.B5, J10.B23, J10.B24, J11.1, J11.3, J11.7, J11.10, J11.12, J12.2, J13.2, J14.6, J14.9, J14.14, J14.20, J14.25, J14.30, J14.34, J14.39, J15.9, J15.10, J16.1, J16.11, J16.16, J17.4 (GND`), J17.8 (GND), J17.MT1, J17.MT2, J17.MT3, J17.MT4, J18.A1, J18.A5, J18.A23, J18.A24, J18.B1, J18.B12, J18.B20, J18.B23, J18.B24, J19.A1, J19.A5, J19.A23, J19.A24, J19.B1, J19.B12, J19.B20, J19.B23, J19.B24, J20.A1, J20.A5, J20.A23, J20.A24, J20.B1, J20.B12, J20.B20, J20.B23, J20.B24, J21.1, J21.3, J22.1, J23.9, J23.10, J24.1, J24.3, J25.1, J26.9, J26.10, J27.1, J27.3, J28.1, LED1.1 (K), LED2.1 (K), LED3.1 (K), LED4.1 (K), LED5.1 (K), Module1.1 (GND), Module1.2 (GND), Module1.7 (GND), Module1.8 (GND), Module1.13 (GND), Module1.14 (GND), Module1.22 (GND), Module1.23 (GND), Module1.32 (GND), Module1.33 (GND), Module1.42 (GND), Module1.43 (GND), Module1.52 (GND), Module1.53 (GND), Module1.59 (GND), Module1.60 (GND), Module1.65 (GND), Module1.66 (GND), Module1.71 (GND), Module1.74 (GND), Module1.98 (GND), Module1.107 (GND), Module1.108 (GND), Module1.113 (GND), Module1.114 (GND), Module1.119 (GND), Module1.120 (GND), Module1.125 (GND), Module1.126 (GND), Module1.131 (GND), Module1.132 (GND), Module1.137 (GND), Module1.138 (GND), Module1.144 (GND), Module1.150 (GND), Module1.155 (GND), Module1.156 (GND), Module1.161 (GND), Module1.162 (GND), Module1.167 (GND), Module1.168 (GND), Module1.173 (GND), Module1.174 (GND), Module1.179 (GND), Module1.180 (GND), Module1.185 (GND), Module1.186 (GND), Module1.191 (GND), Module1.192 (GND), Module1.197 (GND), Module1.198 (GND), PS1.3 (-VIN), PS1.4 (-VOUT), PS2.3 (-VIN), PS2.4 (-VOUT), PS3.5 (-VOUT), PS3.6 (ON/OFF_CONTROL), R2.2, R4.2, R8.2, R10.2, R15.2, R17.2, R21.2, R23.2, R27.2, R29.2, R31.2, R32.2, R33.2, R34.2, R35.2, R36.2, R37.2, R40.2, R41.2, R43.2, R46.1, R47.2, R48.2, U1.6 (GND), U1.11 (GND), U1.13 (NC), U2.6 (GND), U2.11 (GND), U2.13 (NC), U3.6 (GND), U3.11 (GND), U3.13 (NC), U4.J1_22 (GND), U4.J1_42 (GND), U4.J2_24 (GND_1), U4.J2_33 (GND_1), U4.J2_44 (GND_1), U4.J2_57 (GND_1), U4.J2_70 (GND_1), U5.14 (VSS), U5.25 (EXTCLK), U6.10 (GND), U7.5 (GND), U7.10 (nOE), U8.37 (VSS), U9.3 (GND), U9.8 (GND), U10.2 (GND), U11.3 (GND), U12.3 (GND)
GPIO4 RED LED: IC1.1 (IN_1), U4.J2_54 (GPIO_4)
GPIO5 YELLOW LED: IC1.2 (IN_2), U4.J2_56 (GPIO_5)
GPIO6 GREEN LED: IC1.3 (IN_3), U4.J2_58 (GPIO_6)
H7_CAN1_RX: IC2.4 (RXD), U4.J1_51 (CAN1_RX)
H7_CAN1_TX: IC2.1 (TXD), U4.J1_49 (CAN1_TX)
H7_I2C0_SCL: R6.2, R18.2, R24.2, R44.2, U1.4 (A1), U1.5 (A0), U1.9 (SCL), U2.4 (A1), U2.9 (SCL), U3.4 (A1), U3.9 (SCL), U4.J1_46 (I2C0_SCL), U5.26 (SCL)
H7_I2C0_SDA: R11.2, R19.2, R25.2, R42.2, U1.8 (SDA), U2.5 (A0), U2.8 (SDA), U3.8 (SDA), U4.J1_44 (I2C0_SDA), U5.27 (SDA)
LED_GREEN: IC1.14 (OUT_5), J16.10
LED_RED: IC1.16 (OUT_7), J16.8
LED_YELLOW: IC1.15 (OUT_6), J16.9
unnamed: C21.1, D3.C, L1.1, U13.2
unnamed: C22.1, D4.C, L2.1, U14.2
unnamed: C23.1, D5.C, L3.1, U15.2
unnamed: C24.1, D6.C, L4.1, U16.2
unnamed: D1.1 (K), R49.1, TP1.1
unnamed: D2.1 (K), R52.1, TP2.1
unnamed: J7.1 (VBUS), R30.1
unnamed: J11.13, U11.4
unnamed: LED1.2 (A), R5.1
unnamed: LED2.2 (A), R12.1
unnamed: LED3.2 (A), R13.1
unnamed: LED4.2 (A), R26.1
unnamed: LED5.2 (A), R45.1
unnamed: Module1.21 (PI_nLED_Activity), R49.2
unnamed: C26.1, L2.2, PS1.1 (+VIN)
unnamed: C27.1, L3.2, PS2.1 (+VIN)
unnamed: C28.1, L4.2, PS3.1 (+VIN)
unnamed: Q1.3 (D), Q2.2 (S)
unnamed: Q1.2 (S), SW1.3
unnamed: R52.2, U12.4
unnamed: U4.J1_31 (GND), U4.J1_47 (GND), U4.J1_54 (GND)
unnamed: U4.J1_53 (VSYS), U4.J1_64 (VSYS)
unnamed: R43.1, U5.23 (*OE)
unnamed: R32.1, U5.1 (A0)
unnamed: R33.1, U5.2 (A1)
unnamed: R34.1, U5.3 (A2)
unnamed: R35.1, U5.4 (A3)
unnamed: R36.1, U5.5 (A4)
unnamed: R37.1, U5.24 (A5)
unnamed: R38.8, U5.6 (LED0)
unnamed: R38.7, U5.7 (LED1)
unnamed: R38.6, U5.8 (LED2)
unnamed: R38.5, U5.9 (LED3)
unnamed: R39.8, U5.10 (LED4)
unnamed: R39.7, U5.11 (LED5)
unnamed: R39.6, U5.12 (LED6)
unnamed: R39.5, U5.13 (LED7)
unnamed: R47.1, U8.25 (HS_IND/CFG_SEL1)
unnamed: R46.2, U8.35 (RBIAS)
unnamed: R31.1, U8.24 (SCL/SMBCLK/CFG_SEL0)
unnamed: R40.1, U8.22 (SDA/SMBDATA/NON_REM1)
unnamed: R41.1, U8.28 (SUSP_IND/LOCAL_PWR/NON_REM0)
unnamed: C5.1, U8.33 (XTALIN/CLKIN), Y1.1
unnamed: C6.1, U8.32 (XTALOUT), Y1.2
unnamed: U9.1 (D1+), U9.10
unnamed: U9.2 (D1-), U9.9
unnamed: R48.1, U10.5 (ILIM)
unnamed: U17.4 (G), U18.8 (GATE), U19.4 (G)
unnamed: U17.1 (S), U17.2 (S), U17.3 (S), U19.1 (S), U19.2 (S), U19.3 (S)
unnamed: R57.1, U18.5 (*SHDN)
unnamed: R55.2, R56.1, U18.3 (OV)
unnamed: R54.2, R55.1, U18.2 (UV)
unnamed: C35.1, J1.2, U18.7 (VOUT), U19.5 (D), U19.6 (D), U19.7 (D), U19.8 (D)
PWM0: J4.2, R38.1
PWM1: J4.5, R38.2
PWM2: J4.8, R38.3
PWM3: J4.11, R38.4
PWM4: J4.14, R39.1
PWM5: J4.17, R39.2
PWM6: J4.20, R39.3
PWM7: J4.23, R39.4
RPI_GPIO_14_TX: J14.8, Module1.55 (GPIO14), U4.J1_36 (UART0_RX)
RPI_GPIO_15_RX: J14.10, Module1.51 (GPIO15), U4.J1_34 (UART0_TX)
STEPPER_ENABLE: R26.2, R27.1, SW1.4
UT_SIGNAL: J16.3, R20.1
ZIGBEE_IO: Q2.1 (G), R45.2, U6.20 (AD0/DIO0)
